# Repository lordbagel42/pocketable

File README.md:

# Pocketable

<sup><sub>ignore the fact that some of the keycaps are shiny and others are matte. blender is not happy with me.</sub></sup>

if a corne and a zsa voyager had a child\_

This project was made for one primary reason: my old split keyboard design kinda sucked to make layouts for. The thumb cluster was horrible. This, however, will function with ZSA Voyager layouts, which are generally shared publicly and well-tested.

This will be for sale eventually. Please reply to [issue 1](https://github.com/lordbagel42/pocketable/issues/1) if you would like to buy one. Cost will be around $240 per keyboard.

## but why?

This keyboards a little special compared to most, for one reason: it's almost all made in-house by me. I'll be machining the brass plate myself along with the wooden base case, plus laser-cutting the acrylic LED cover myself. It's also all hand soldered and one day will have custom keycaps. For now though I've been graciously sponsored with black keycaps.

# BOM

View the BOM at [this google sheet](https://docs.google.com/spreadsheets/d/1JvyBpCuiH7XgFo-gO215HGFeqtSEhnPSUs8fcJy509Q/edit?gid=363512385#gid=363512385). Total cost at time of writing this README is ~$250

## more photos :3

heres the pcb design!

silkscreen art will be included for mine, however I won't be showing it in this repo as it contains a lil PII :3

## left half schematic

## right half schematic

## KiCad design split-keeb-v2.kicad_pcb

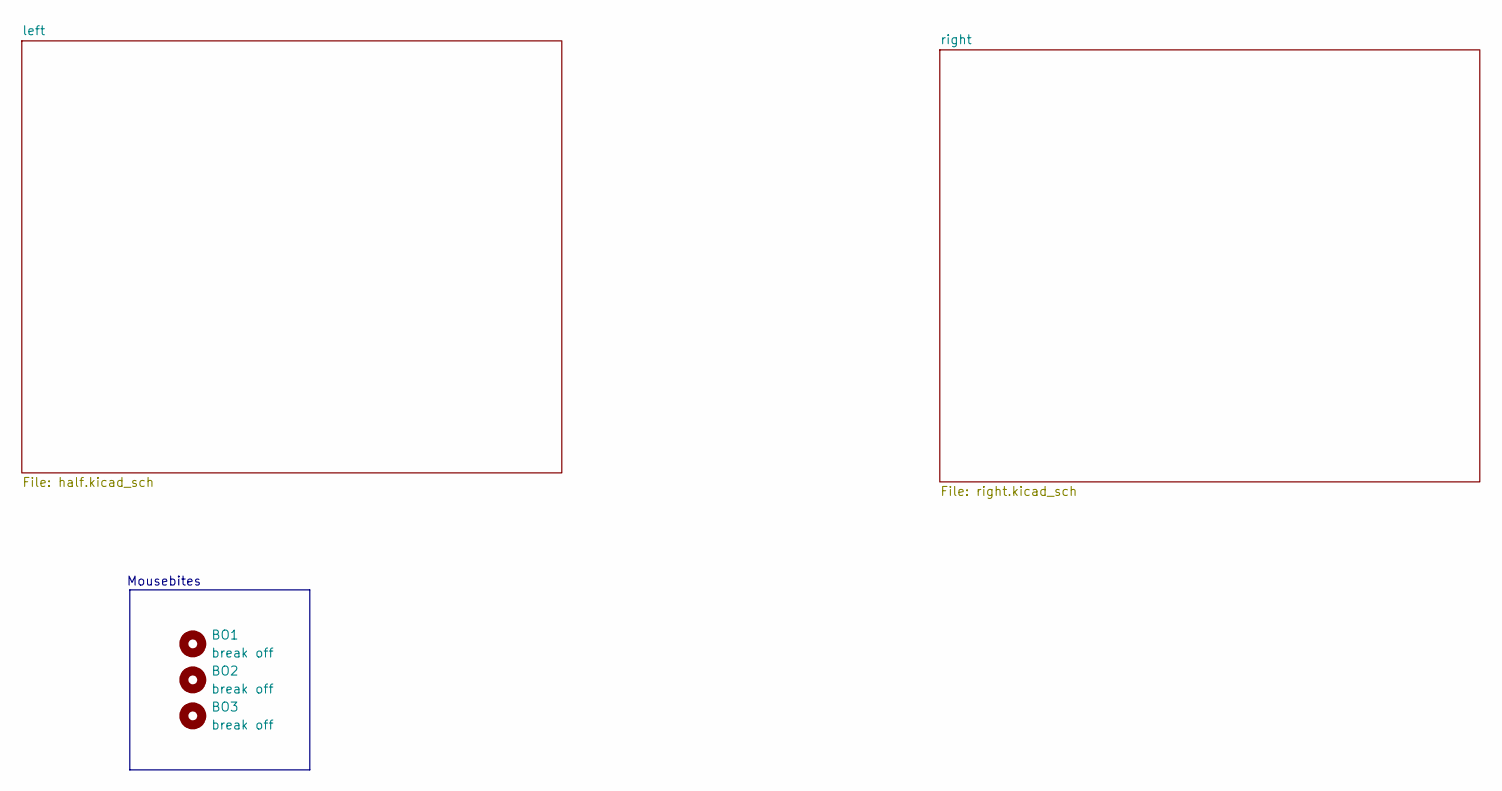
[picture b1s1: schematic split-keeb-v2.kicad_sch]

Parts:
BO1, BO2, BO3: break off; mouse-bite-5mm-slot

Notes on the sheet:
Mousebites

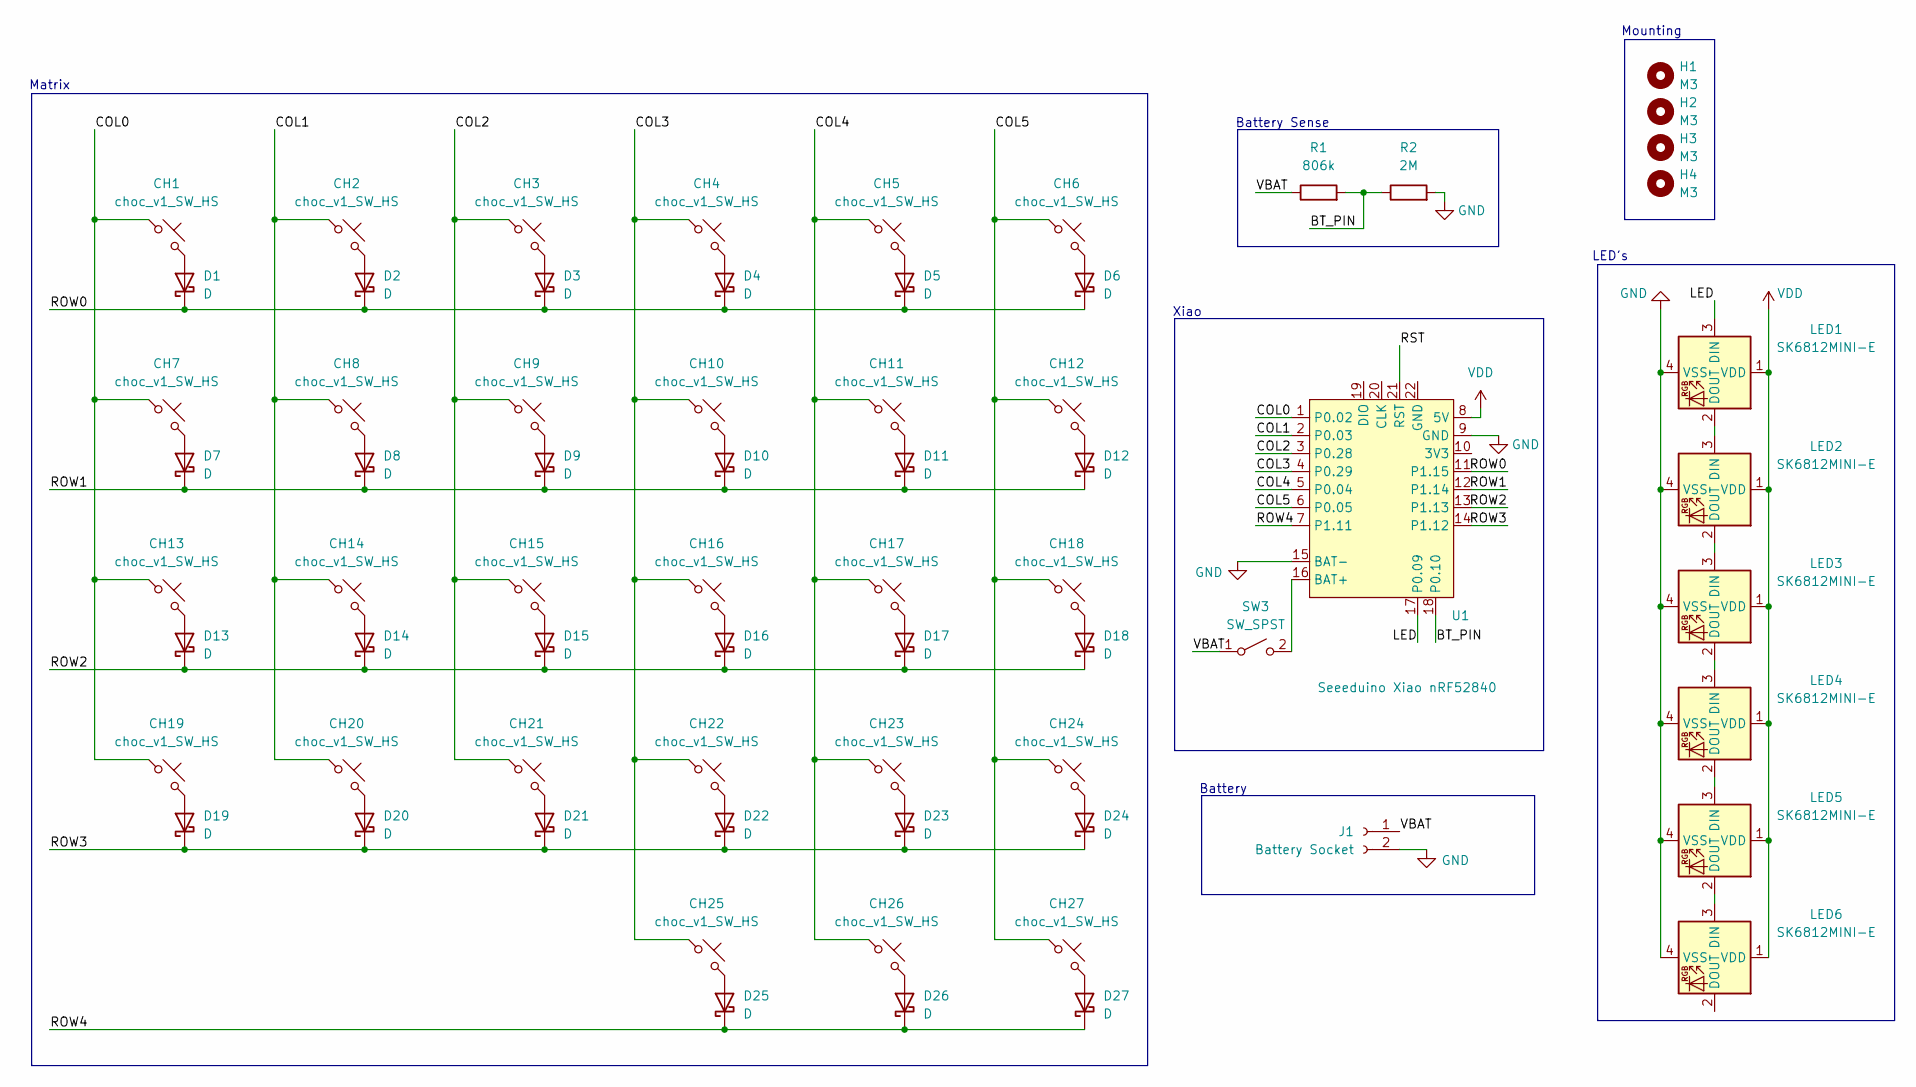
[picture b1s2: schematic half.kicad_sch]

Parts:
CH1, CH2, CH3, CH4, CH5, CH6, CH7, CH8, CH9, CH10, CH11, CH12, CH13, CH14, CH15, CH16, CH17, CH18, CH19, CH20, CH21, CH22, CH23, CH24, CH25, CH26, CH27: choc_v1_SW_HS; SW_choc_v1_HS_CPG135001S30_1u
D1, D2, D3, D4, D5, D6, D7, D8, D9, D10, D11, D12, D13, D14, D15, D16, D17, D18, D19, D20, D21, D22, D23, D24, D25, D26, D27: D; D_SOD-123
H1, H2, H3, H4: M3; MountingHole_3.2mm_M3
J1: Battery Socket; CON_JST_ACH_BM02B
LED1, LED2, LED3, LED4, LED5, LED6: SK6812MINI-E; LED_6028R
R1: 806k; R_0805_2012Metric
R2: 2M; R_0805_2012Metric
SW3: SW_SPST; SW_SPDT_PCM12
U1: Seeeduino Xiao nRF52840; Xiao_nRF52840_ACH

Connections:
/left/BT_PIN: R1.2, R2.1, U1.18 (P0.10)
/left/COL0: CH1.1, CH7.1, CH13.1, CH19.1, U1.1 (P0.02)
/left/COL1: CH2.1, CH8.1, CH14.1, CH20.1, U1.2 (P0.03)
/left/COL2: CH3.1, CH9.1, CH15.1, CH21.1, U1.3 (P0.28)
/left/COL3: CH4.1, CH10.1, CH16.1, CH22.1, CH25.1, U1.4 (P0.29)
/left/COL4: CH5.1, CH11.1, CH17.1, CH23.1, CH26.1, U1.5 (P0.04)
/left/COL5: CH6.1, CH12.1, CH18.1, CH24.1, CH27.1, U1.6 (P0.05)
/left/ROW0: D1.1 (K), D2.1 (K), D3.1 (K), D4.1 (K), D5.1 (K), D6.1 (K), U1.11 (P1.15)
/left/ROW1: D7.1 (K), D8.1 (K), D9.1 (K), D10.1 (K), D11.1 (K), D12.1 (K), U1.12 (P1.14)
/left/ROW2: D13.1 (K), D14.1 (K), D15.1 (K), D16.1 (K), D17.1 (K), D18.1 (K), U1.13 (P1.13)
/left/ROW3: D19.1 (K), D20.1 (K), D21.1 (K), D22.1 (K), D23.1 (K), D24.1 (K), U1.14 (P1.12)
/left/ROW4: D25.1 (K), D26.1 (K), D27.1 (K), U1.7 (P1.11)
/left/RST: U1.21 (RST)
/left/VBAT: J1.1, R1.1, SW3.1 (A)
GND: J1.2, LED1.4 (VSS), LED2.4 (VSS), LED3.4 (VSS), LED4.4 (VSS), LED5.4 (VSS), LED6.4 (VSS), R2.2, U1.9 (GND), U1.15 (BAT-); also elsewhere on the board
unnamed: CH1.2, D1.2 (A)
unnamed: CH2.2, D2.2 (A)
unnamed: CH3.2, D3.2 (A)
unnamed: CH4.2, D4.2 (A)
unnamed: CH5.2, D5.2 (A)
unnamed: CH6.2, D6.2 (A)
unnamed: CH7.2, D7.2 (A)
unnamed: CH8.2, D8.2 (A)
unnamed: CH9.2, D9.2 (A)
unnamed: CH10.2, D10.2 (A)
unnamed: CH11.2, D11.2 (A)
unnamed: CH12.2, D12.2 (A)
unnamed: CH13.2, D13.2 (A)
unnamed: CH14.2, D14.2 (A)
unnamed: CH15.2, D15.2 (A)
unnamed: CH16.2, D16.2 (A)
unnamed: CH17.2, D17.2 (A)
unnamed: CH18.2, D18.2 (A)
unnamed: CH19.2, D19.2 (A)
unnamed: CH20.2, D20.2 (A)
unnamed: CH21.2, D21.2 (A)
unnamed: CH22.2, D22.2 (A)
unnamed: CH23.2, D23.2 (A)
unnamed: CH24.2, D24.2 (A)
unnamed: CH25.2, D25.2 (A)
unnamed: CH26.2, D26.2 (A)
unnamed: CH27.2, D27.2 (A)
unnamed 83: LED1.1 (VDD), LED2.1 (VDD), LED3.1 (VDD), LED4.1 (VDD), LED5.1 (VDD), LED6.1 (VDD), U1.8 (5V); also elsewhere on the board
unnamed: LED1.2 (DOUT), LED2.3 (DIN)
unnamed 85: LED1.3 (DIN), U1.17 (P0.09); also elsewhere on the board
unnamed: LED2.2 (DOUT), LED3.3 (DIN)
unnamed: LED3.2 (DOUT), LED4.3 (DIN)
unnamed: LED4.2 (DOUT), LED5.3 (DIN)
unnamed: LED5.2 (DOUT), LED6.3 (DIN)
unnamed 91: U1.17 (P0.09); also elsewhere on the board
unnamed 93: U1.8 (5V); also elsewhere on the board
unnamed: SW3.2 (B), U1.16 (BAT+)

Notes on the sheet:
Battery Sense
Xiao
LED's
Mounting
Battery
Matrix

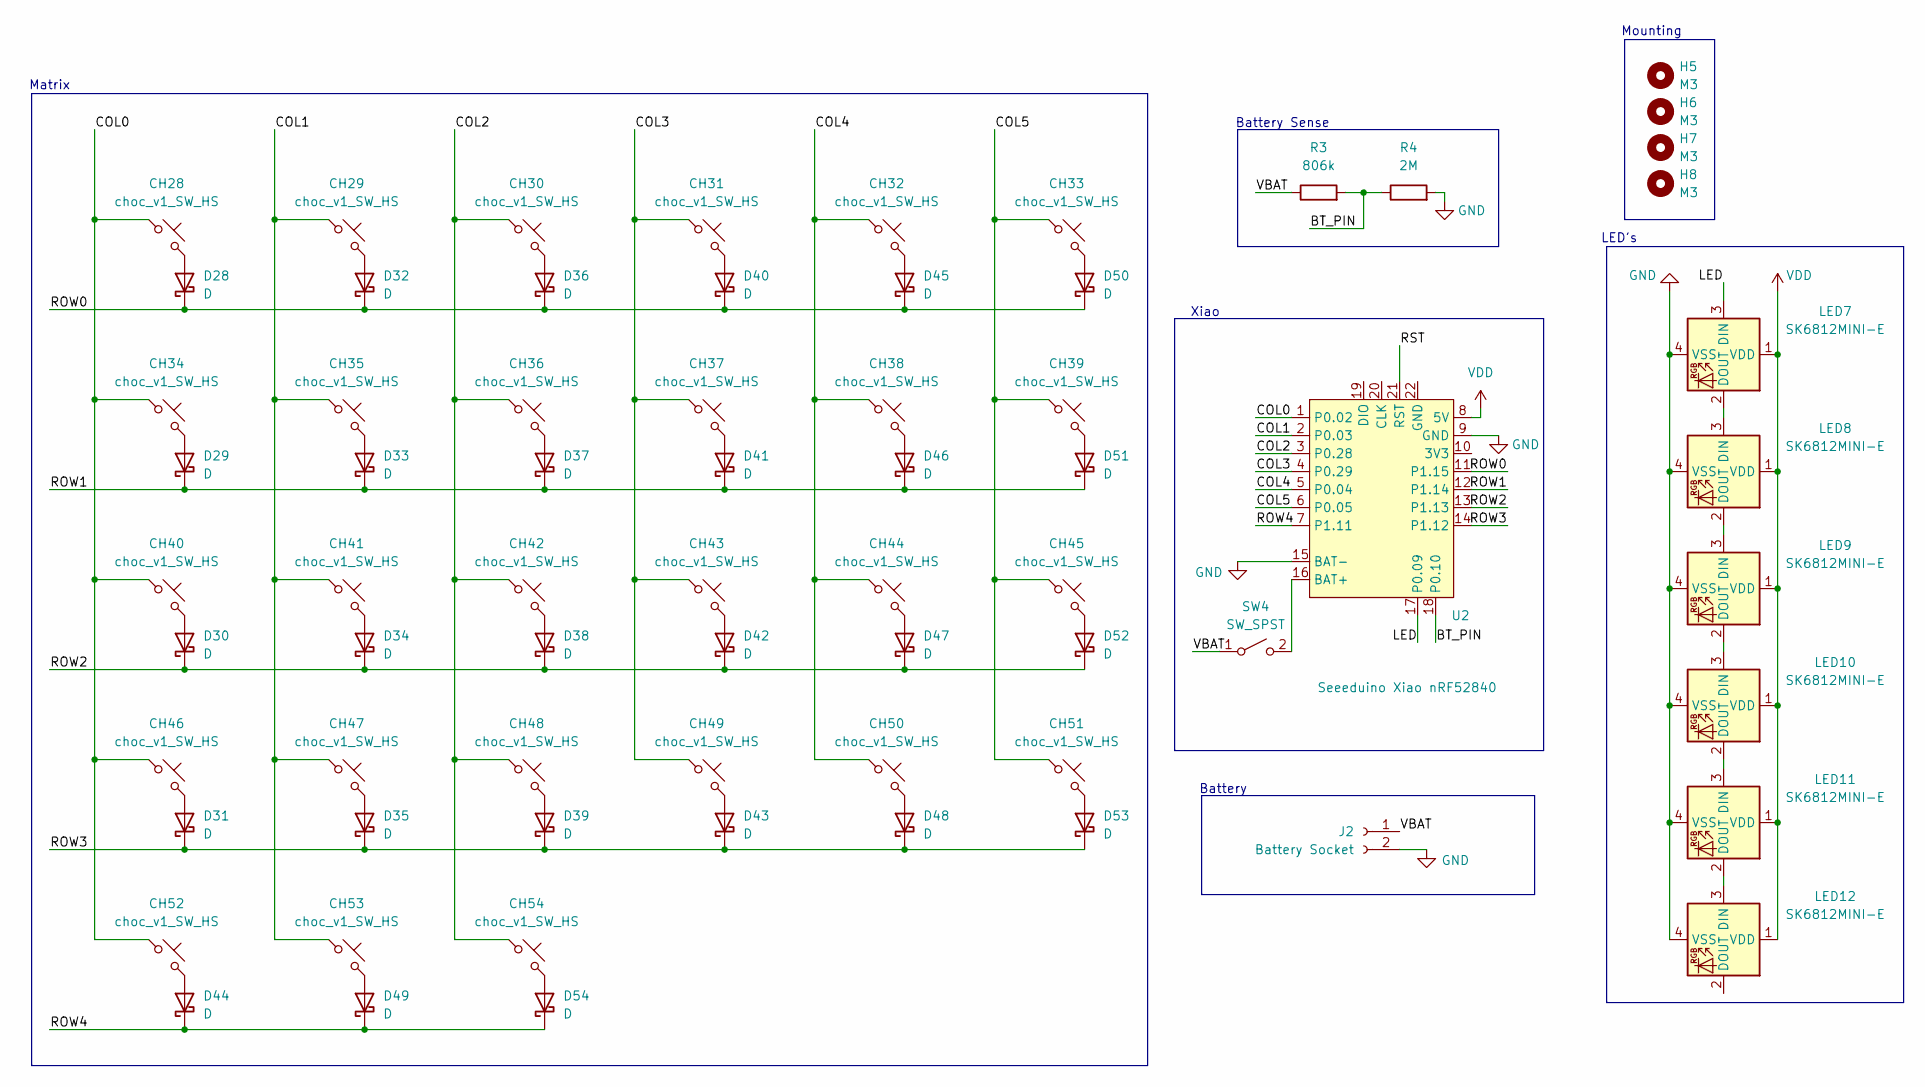
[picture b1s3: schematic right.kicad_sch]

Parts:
CH28, CH29, CH30, CH31, CH32, CH33, CH34, CH35, CH36, CH37, CH38, CH39, CH40, CH41, CH42, CH43, CH44, CH45, CH46, CH47, CH48, CH49, CH50, CH51, CH52, CH53, CH54: choc_v1_SW_HS; SW_choc_v1_HS_CPG135001S30_1u
D28, D29, D30, D31, D32, D33, D34, D35, D36, D37, D38, D39, D40, D41, D42, D43, D44, D45, D46, D47, D48, D49, D50, D51, D52, D53, D54: D; D_SOD-123
H5, H6, H7, H8: M3; MountingHole_3.2mm_M3
J2: Battery Socket; CON_JST_ACH_BM02B
LED7, LED8, LED9, LED10, LED11, LED12: SK6812MINI-E; LED_6028R
R3: 806k; R_0805_2012Metric
R4: 2M; R_0805_2012Metric
SW4: SW_SPST; SW_SPDT_PCM12
U2: Seeeduino Xiao nRF52840; Xiao_nRF52840_ACH

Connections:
/right/BT_PIN: R3.2, R4.1, U2.18 (P0.10)
/right/COL0: CH28.1, CH34.1, CH40.1, CH46.1, CH52.1, U2.1 (P0.02)
/right/COL1: CH29.1, CH35.1, CH41.1, CH47.1, CH53.1, U2.2 (P0.03)
/right/COL2: CH30.1, CH36.1, CH42.1, CH48.1, CH54.1, U2.3 (P0.28)
/right/COL3: CH31.1, CH37.1, CH43.1, CH49.1, U2.4 (P0.29)
/right/COL4: CH32.1, CH38.1, CH44.1, CH50.1, U2.5 (P0.04)
/right/COL5: CH33.1, CH39.1, CH45.1, CH51.1, U2.6 (P0.05)
/right/ROW0: D28.1 (K), D32.1 (K), D36.1 (K), D40.1 (K), D45.1 (K), D50.1 (K), U2.11 (P1.15)
/right/ROW1: D29.1 (K), D33.1 (K), D37.1 (K), D41.1 (K), D46.1 (K), D51.1 (K), U2.12 (P1.14)
/right/ROW2: D30.1 (K), D34.1 (K), D38.1 (K), D42.1 (K), D47.1 (K), D52.1 (K), U2.13 (P1.13)
/right/ROW3: D31.1 (K), D35.1 (K), D39.1 (K), D43.1 (K), D48.1 (K), D53.1 (K), U2.14 (P1.12)
/right/ROW4: D44.1 (K), D49.1 (K), D54.1 (K), U2.7 (P1.11)
/right/RST: U2.21 (RST)
/right/VBAT: J2.1, R3.1, SW4.1 (A)
GND: J2.2, LED7.4 (VSS), LED8.4 (VSS), LED9.4 (VSS), LED10.4 (VSS), LED11.4 (VSS), LED12.4 (VSS), R4.2, U2.9 (GND), U2.15 (BAT-); also elsewhere on the board
unnamed: CH28.2, D28.2 (A)
unnamed: CH34.2, D29.2 (A)
unnamed: CH40.2, D30.2 (A)
unnamed: CH46.2, D31.2 (A)
unnamed: CH29.2, D32.2 (A)
unnamed: CH35.2, D33.2 (A)
unnamed: CH41.2, D34.2 (A)
unnamed: CH47.2, D35.2 (A)
unnamed: CH30.2, D36.2 (A)
unnamed: CH36.2, D37.2 (A)
unnamed: CH42.2, D38.2 (A)
unnamed: CH48.2, D39.2 (A)
unnamed: CH31.2, D40.2 (A)
unnamed: CH37.2, D41.2 (A)
unnamed: CH43.2, D42.2 (A)
unnamed: CH49.2, D43.2 (A)
unnamed: CH52.2, D44.2 (A)
unnamed: CH32.2, D45.2 (A)
unnamed: CH38.2, D46.2 (A)
unnamed: CH44.2, D47.2 (A)
unnamed: CH50.2, D48.2 (A)
unnamed: CH53.2, D49.2 (A)
unnamed: CH33.2, D50.2 (A)
unnamed: CH39.2, D51.2 (A)
unnamed: CH45.2, D52.2 (A)
unnamed: CH51.2, D53.2 (A)
unnamed: CH54.2, D54.2 (A)
unnamed 83: U2.8 (5V); also elsewhere on the board
unnamed 85: U2.17 (P0.09); also elsewhere on the board
unnamed: LED7.2 (DOUT), LED8.3 (DIN)
unnamed 91: LED7.3 (DIN), U2.17 (P0.09); also elsewhere on the board
unnamed: LED8.2 (DOUT), LED9.3 (DIN)
unnamed 93: LED7.1 (VDD), LED8.1 (VDD), LED9.1 (VDD), LED10.1 (VDD), LED11.1 (VDD), LED12.1 (VDD), U2.8 (5V); also elsewhere on the board
unnamed: LED10.2 (DOUT), LED11.3 (DIN)
unnamed: LED9.2 (DOUT), LED10.3 (DIN)
unnamed: LED11.2 (DOUT), LED12.3 (DIN)
unnamed: SW4.2 (B), U2.16 (BAT+)

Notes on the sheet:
LED's
Battery Sense
Xiao
Mounting
Battery
Matrix

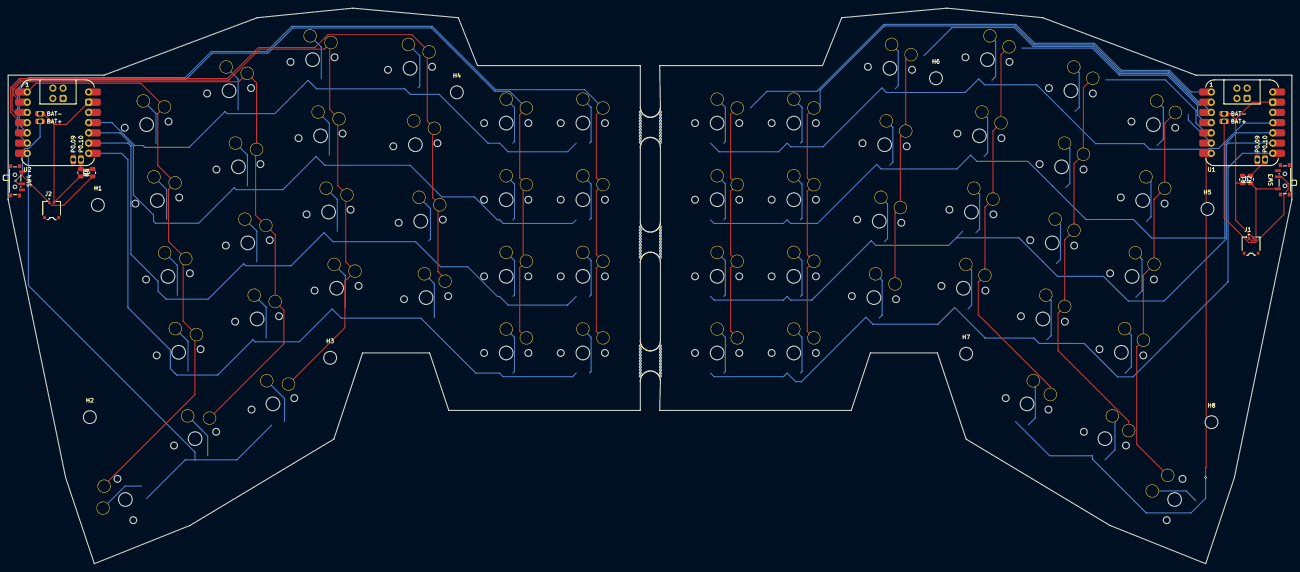
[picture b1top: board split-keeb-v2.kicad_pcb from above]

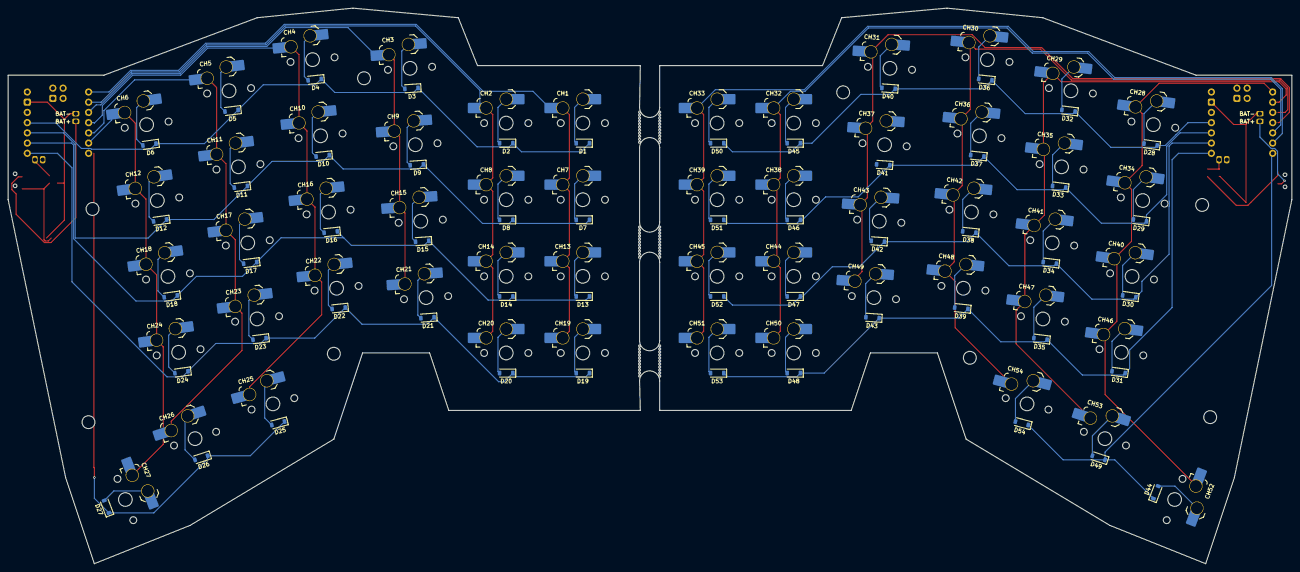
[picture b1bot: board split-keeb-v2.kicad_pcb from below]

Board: 2 copper layers, 319.1 x 138.1 mm, 129 parts (108 on the bottom side), 83 nets.

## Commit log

2025-12-06 bom, readme ish
2025-12-06 oopsies forgot to add the CAD lol
2025-12-06 we ain't getting to prototype with this one
2025-12-06 friggin blenderrrrrrrrr
2025-12-26 lfs here we go
2026-01-15 include schematic pics
2026-02-07 fix RENDERS/
2026-02-07 Add PNG and STEP files to Git LFS tracking
    Amp-Thread-ID: https://ampcode.com/threads/T-f1c5a740-9b84-4d3c-b824-d55490b994a5
2026-02-07 Remove git lfs and compress render images
    Amp-Thread-ID: https://ampcode.com/threads/T-019c37a1-df57-7555-86bd-4a8d9f45d67f
